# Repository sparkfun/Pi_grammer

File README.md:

SparkFun Pi AVR Programmer HAT
========================================

[*SparkFun Pi AVR Programmer HAT (DEV-14747)*](https://www.sparkfun.com/products/14747)

A shield for Raspberry Pi 2, used for programming AVR ICs. Includes capsense pad to engage, 2x3 ISP header for connectivity and status LEDs.

Documentation
--------------
* **[Hookup Guide](https://learn.sparkfun.com/tutorials/pi-avr-programmer-hat-hookup-guide)** - Basic hookup guide for the Pi AVR Programmer Hat.
* **[Raspberry Pi Stand-Alone Programmer](https://learn.sparkfun.com/tutorials/raspberry-pi-stand-alone-programmer)** - more information about the prototype can be found in the article.

Additional Notes
--------------
This project originated from Adafruits tutorial here:

https://learn.adafruit.com/program-an-avr-or-arduino-using-raspberry-pi-gpio-pins/overview

This shield makes it a bit easier to program AVRs with a headless Raspberry Pi.

This repo also contains some other useful files:

* **RCLOCAL** - calls /home/pi/test.py and ensure that this python module will run automatically at boot up (useful when running headless)

* **AVRDUDE config file** - sets the GPIO used for programming (in avrdude) to work with the shield design. It's located at the very end of this file.

* **test.py** - the python module that is auto called during bootup. This also listens to the capsense IC and engages programming when p ressed.

**Note:** test.py called pi_program.sh to actually begin programming.

**Note:** test.py also checks for MEDIA drives plugged into the USB ports of the Raspi. If there is a HEX file on the MEDIA drive (any name, it just has to have the ".hex" extension) it will copy it in and use that for programming.

KEYWORDS: RASPI PROGRAMMER

Troubleshooting Tips
--------------

1) USB port issues. If you are having trouble with com port enumeration. That is, you are plugging in something like an FTDI serial basic, and the Raspi will not recognize it. This may be fixed by using one of SparkFun Cerberus USB hub cables. We found that after plugging in 20+ FTDI basics into a pi, then it stops recognizing the devices. But if you use a hub (like the cerberus) inbetween the pi USB and the serial bridge IC, then it always pops up as "/dev/ttyUSB0" for 1000s of boards in a row. Wahoo!

[SparkFun Cerberus USB Cable](https://www.sparkfun.com/products/12016)

License Information
-------------------

This product is _**open source**_! 

Please review the LICENSE.md file for license information. 

If you have any questions or concerns on licensing, please contact techsupport@sparkfun.com.

Distributed as-is; no warranty is given.

- Your friends at SparkFun.

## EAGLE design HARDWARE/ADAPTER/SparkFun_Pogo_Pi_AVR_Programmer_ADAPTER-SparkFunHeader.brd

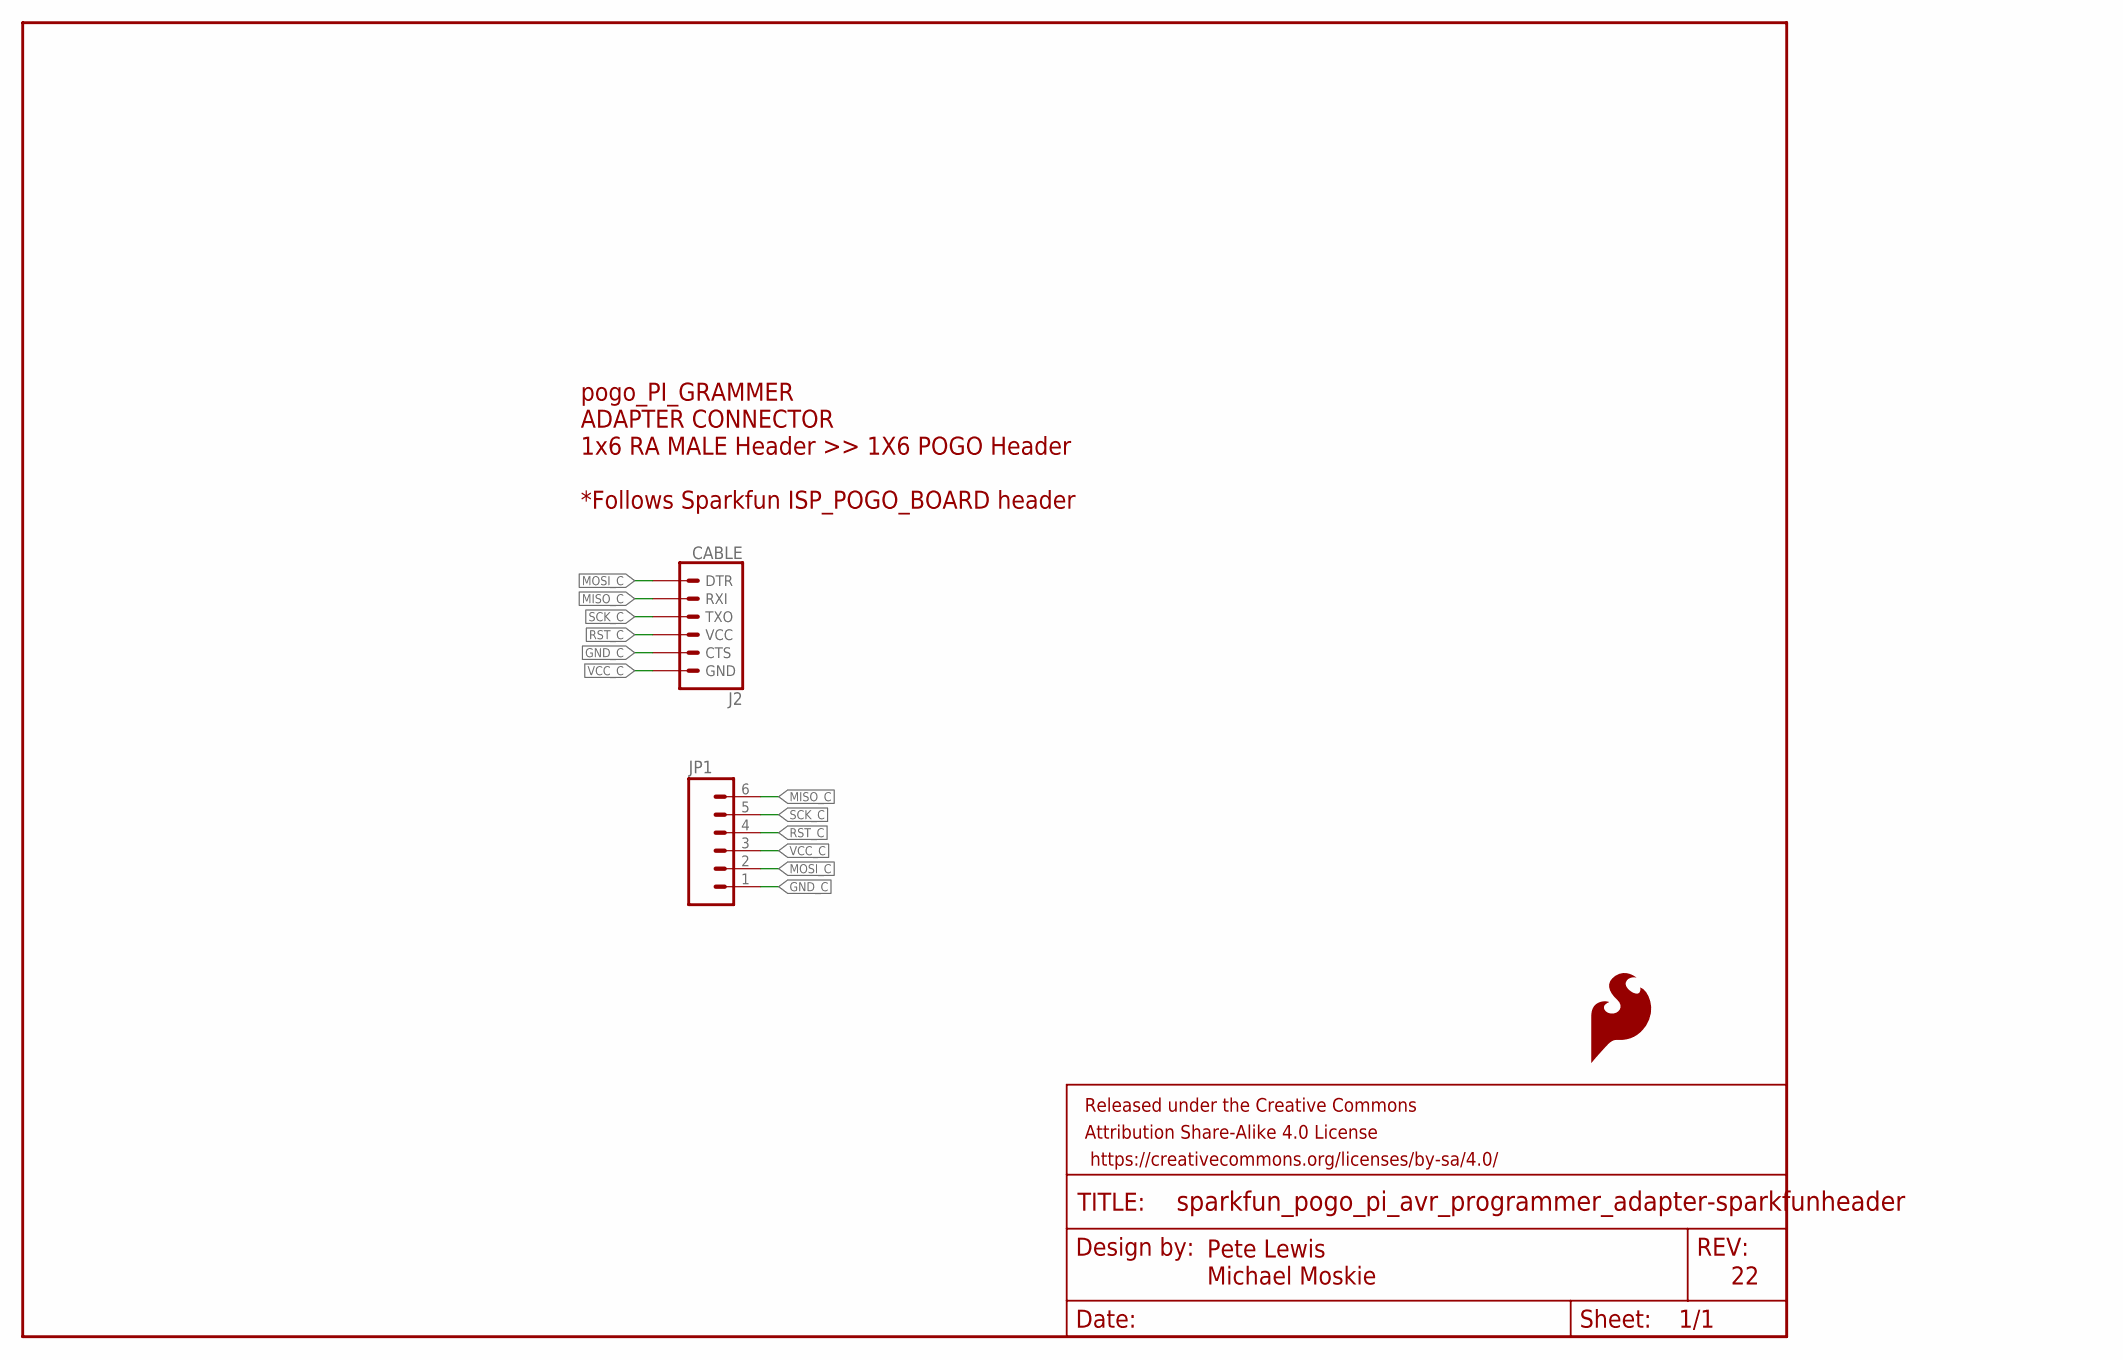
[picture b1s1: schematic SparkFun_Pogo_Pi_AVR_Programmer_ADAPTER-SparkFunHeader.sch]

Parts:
FRAME1: FRAME-LETTER; CREATIVE_COMMONS
J2: CABLE; 1X06-SMD_RA_MALE
JP1: M06POLAR; MOLEX-1X6
LOGO1: SFE_LOGO_FLAME.1_INCH; SFE_LOGO_FLAME_.1

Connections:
GND_C: J2.5 (CTS), JP1.1
MISO_C: J2.2 (RXI), JP1.6
MOSI_C: J2.1 (DTR), JP1.2
RST_C: J2.4 (VCC), JP1.4
SCK_C: J2.3 (TXO), JP1.5
VCC_C: J2.6 (GND), JP1.3

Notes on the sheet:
pogo_PI_GRAMMER ADAPTER CONNECTOR 1x6 RA MALE Header >> 1X6 POGO Header *Follows Sparkfun ISP_POGO_BOARD header
Pete Lewis Michael Moskie

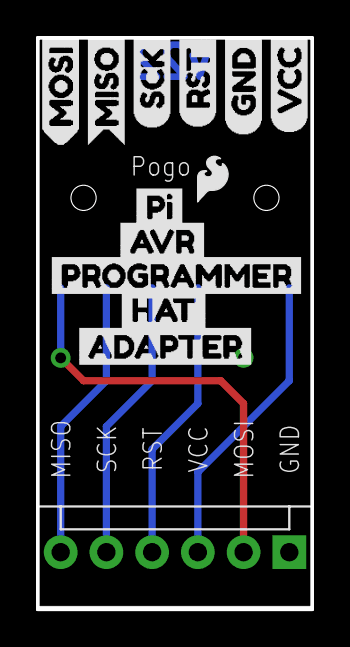
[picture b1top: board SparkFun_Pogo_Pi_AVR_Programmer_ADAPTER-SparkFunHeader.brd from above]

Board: 2 copper layers, 15.2 x 31.8 mm, 15 parts (1 on the bottom side), 6 nets.

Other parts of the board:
U$1: GND1
U$2: MISO5
U$3: MOSI4
U$4: RST2
U$5: SCK3
U$6: VCC0
U$7: PI0
U$8: AVR1
U$9: PROGRAMMER2
U$10: HAT3
U$11: ADAPTER4

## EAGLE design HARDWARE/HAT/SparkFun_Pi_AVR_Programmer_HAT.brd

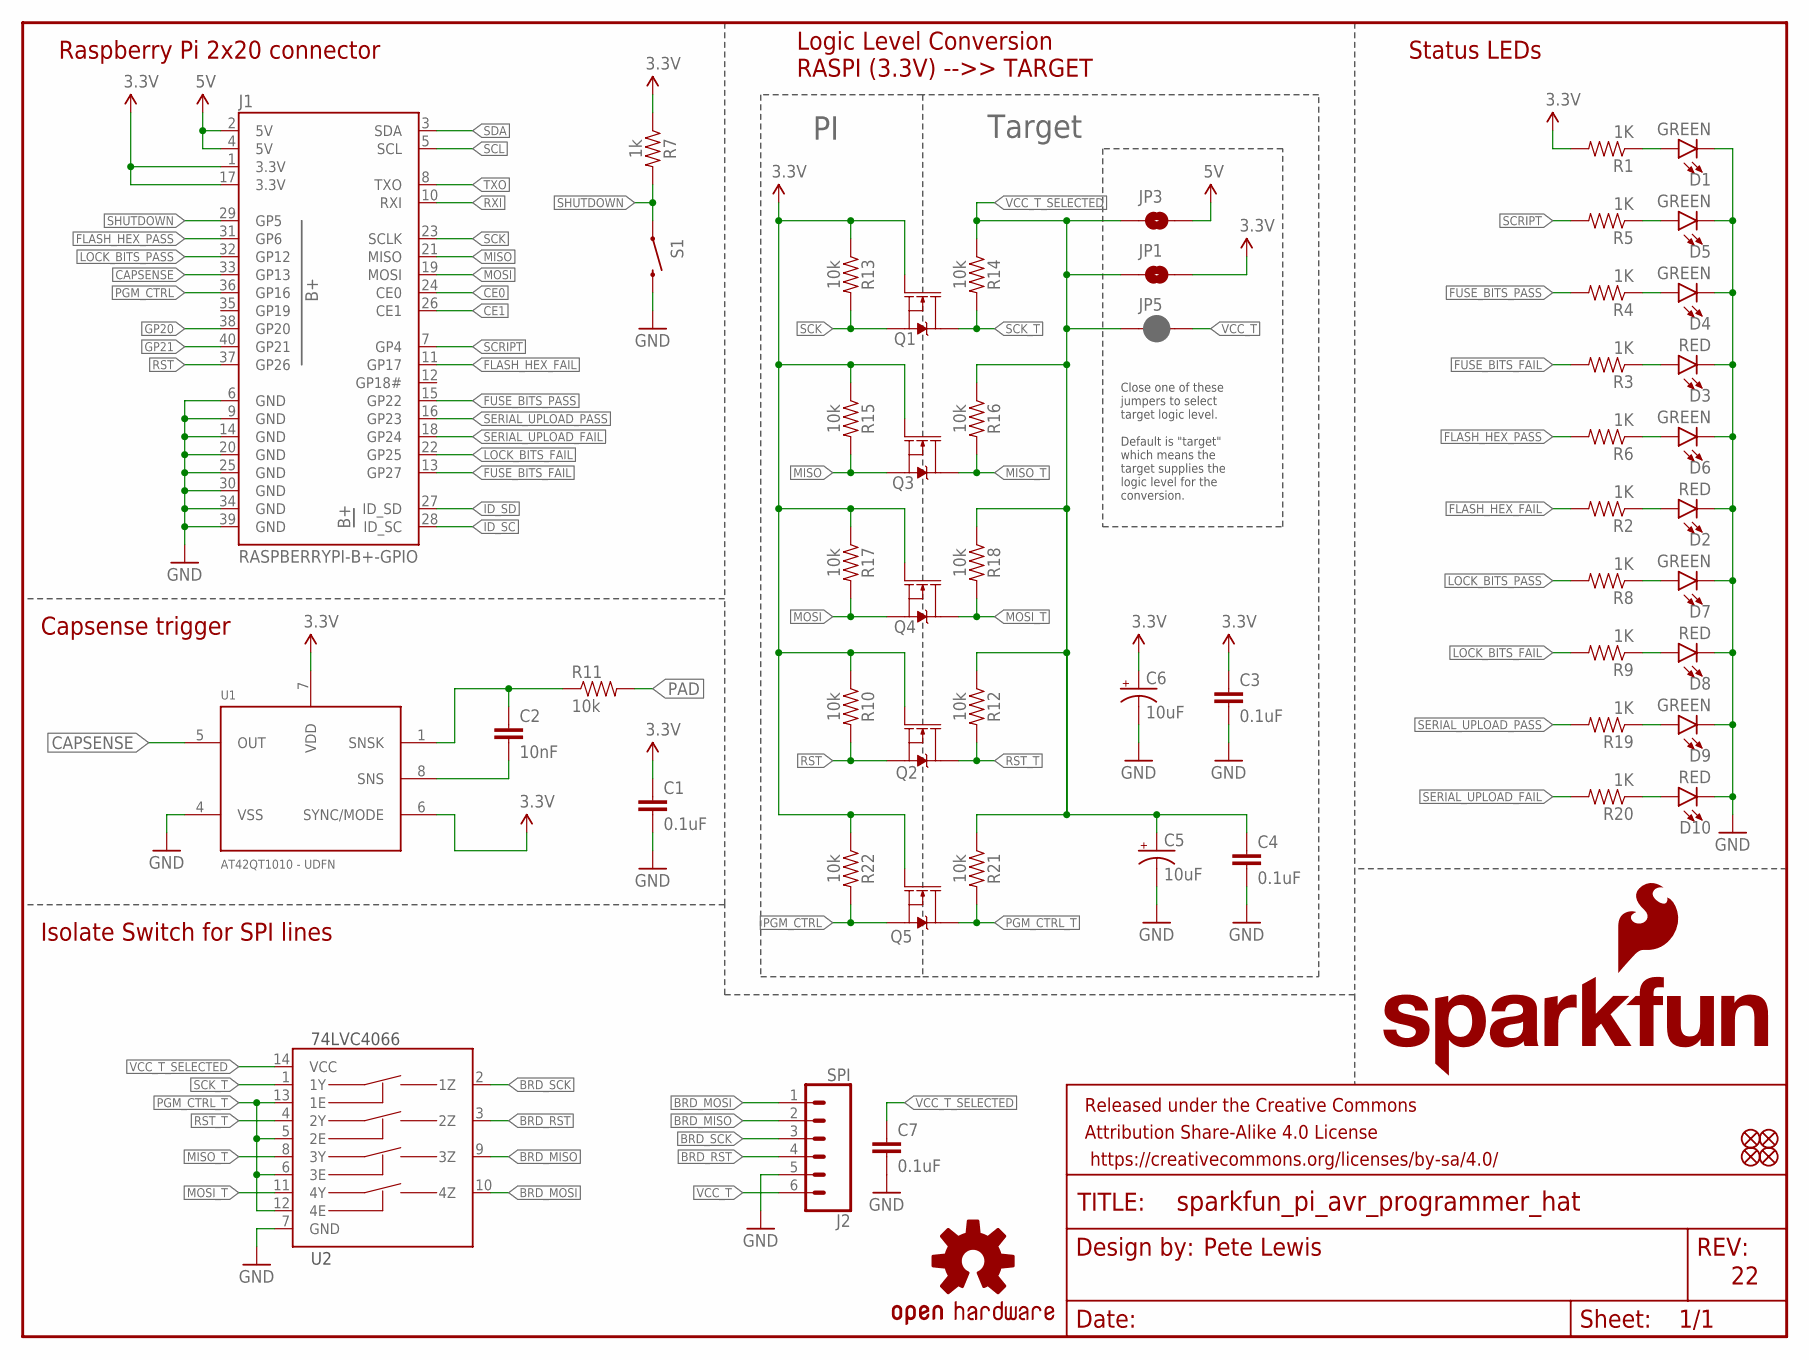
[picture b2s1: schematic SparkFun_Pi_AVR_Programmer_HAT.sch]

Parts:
C1: 0.1uF; 0603-CAP
C2: 10nF; 0603-CAP
C3, C4, C7: 0.1uF; 0603
C5, C6: 10uF; EIA3216
D1, D4, D5, D6, D7, D9: GREEN; LED-1206
D2, D3, D8, D10: RED; LED-1206
FD1, FD2, FD3, FD4: FIDUCIALUFIDUCIAL; FIDUCIAL-MICRO
FRAME1: FRAME-LETTER; CREATIVE_COMMONS
J1: RASPBERRYPI-B+-GPIO; 2X20-SHROUDED
J2: SPI; 1X06-SMD_RA_MALE
JP1, JP3: JUMPER-SMT_2_NO_SILK; SMT-JUMPER_2_NO_SILK
JP5: JUMPER-SMT_2_NC_PASTE_SILK; SMT-JUMPER_2_NC_PASTE_SILK
LOGO1: SFE_LOGO_FLAME.2_INCH; SFE_LOGO_FLAME_.2
LOGO2: OSHW-LOGOL; OSHW-LOGO-L
LOGO3: SFE_LOGO_NAME.6_INCH; SFE_LOGO_NAME_.6
Q1, Q2, Q3, Q4, Q5: 220mA/50V/3.5Ω; SOT23-3
R1, R2, R3, R4, R5, R6, R8, R9, R19, R20: 1K; 0603-RES
R7: 1k; 0603
R10, R12, R13, R14, R15, R16, R17, R18, R21, R22: 10k; 0603
R11: 10k; 0603-RES
S1: SWITCH-MOMENTARY-2SMD; TACTILE-SWITCH-SMD
U1: AT42QT1010 - UDFN; UDFN/USON_8_PAD
U2: 74LVC4066; SO14

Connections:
3.3V: C1.1, C3.1, C6.+, J1.1 (3.3V), J1.17 (3.3V), JP1.2, Q1.1 (G), Q2.1 (G), Q3.1 (G), Q4.1 (G), Q5.1 (G), R1.2, R7.1, R10.1, R13.1, R15.1, R17.1, R22.1, U1.6 (SYNC/MODE), U1.7 (VDD)
5V: J1.2 (5V), J1.4 (5V), JP3.2
BRD_MISO: J2.2, U2.9 (3Z)
BRD_MOSI: J2.1, U2.10 (4Z)
BRD_RST: J2.4, U2.3 (2Z)
BRD_SCK: J2.3, U2.2 (1Z)
CAPSENSE: J1.33 (GP13), U1.5 (OUT)
CE0: J1.24 (CE0)
CE1: J1.26 (CE1)
FLASH_HEX_FAIL: J1.11 (GP17), R2.2
FLASH_HEX_PASS: J1.31 (GP6), R6.2
FUSE_BITS_FAIL: J1.13 (GP27), R3.2
FUSE_BITS_PASS: J1.15 (GP22), R4.2
GND: C1.2, C3.2, C4.2, C5.-, C6.-, C7.2, D1.C, D2.C, D3.C, D4.C, D5.C, D6.C, D7.C, D8.C, D9.C, D10.C, J1.6 (GND), J1.9 (GND), J1.14 (GND), J1.20 (GND), J1.25 (GND), J1.30 (GND), J1.34 (GND), J1.39 (GND), J2.5, S1.3 (2), U1.4 (VSS), U2.7 (GND)
GP20: J1.38 (GP20)
GP21: J1.40 (GP21)
ID_SC: J1.28 (ID_SC)
ID_SD: J1.27 (ID_SD)
LOCK_BITS_FAIL: J1.22 (GP25), R9.2
LOCK_BITS_PASS: J1.32 (GP12), R8.2
MISO: J1.21 (MISO), Q3.2 (S), R15.2
MISO_T: Q3.3 (D), R16.2, U2.8 (3Y)
MOSI: J1.19 (MOSI), Q4.2 (S), R17.2
MOSI_T: Q4.3 (D), R18.2, U2.11 (4Y)
unnamed: D6.A, R6.1
unnamed: D1.A, R1.1
unnamed: D2.A, R2.1
unnamed: D3.A, R3.1
unnamed: D7.A, R8.1
unnamed: D4.A, R4.1
unnamed: D5.A, R5.1
unnamed: D8.A, R9.1
unnamed: C2.2, U1.8 (SNS)
unnamed: C2.1, R11.1, U1.1 (SNSK)
unnamed: D9.A, R19.1
unnamed: D10.A, R20.1
PAD: R11.2
PGM_CTRL: J1.36 (GP16), Q5.2 (S), R22.2
PGM_CTRL_T: Q5.3 (D), R21.2, U2.5 (2E), U2.6 (3E), U2.12 (4E), U2.13 (1E)
RST: J1.37 (GP26), Q2.2 (S), R10.2
RST_T: Q2.3 (D), R12.2, U2.4 (2Y)
RXI: J1.10 (RXI)
SCK: J1.23 (SCLK), Q1.2 (S), R13.2
SCK_T: Q1.3 (D), R14.2, U2.1 (1Y)
SCL: J1.5 (SCL)
SCRIPT: J1.7 (GP4), R5.2
SDA: J1.3 (SDA)
SERIAL_UPLOAD_FAIL: J1.18 (GP24), R20.2
SERIAL_UPLOAD_PASS: J1.16 (GP23), R19.2
SHUTDOWN: J1.29 (GP5), R7.2, S1.1
TXO: J1.8 (TXO)
VCC_T: J2.6, JP5.2
VCC_T_SELECTED: C4.1, C5.+, C7.1, JP1.1, JP3.1, JP5.1, R12.1, R14.1, R16.1, R18.1, R21.1, U2.14 (VCC)

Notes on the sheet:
Raspberry Pi 2x20 connector
Pete Lewis
Status LEDs
Capsense trigger
Target
Logic Level Conversion RASPI (3.3V) -->> TARGET
Isolate Switch for SPI lines
Close one of these jumpers to select target logic level. Default is "target" which means the target supplies the logic level for the conversion.

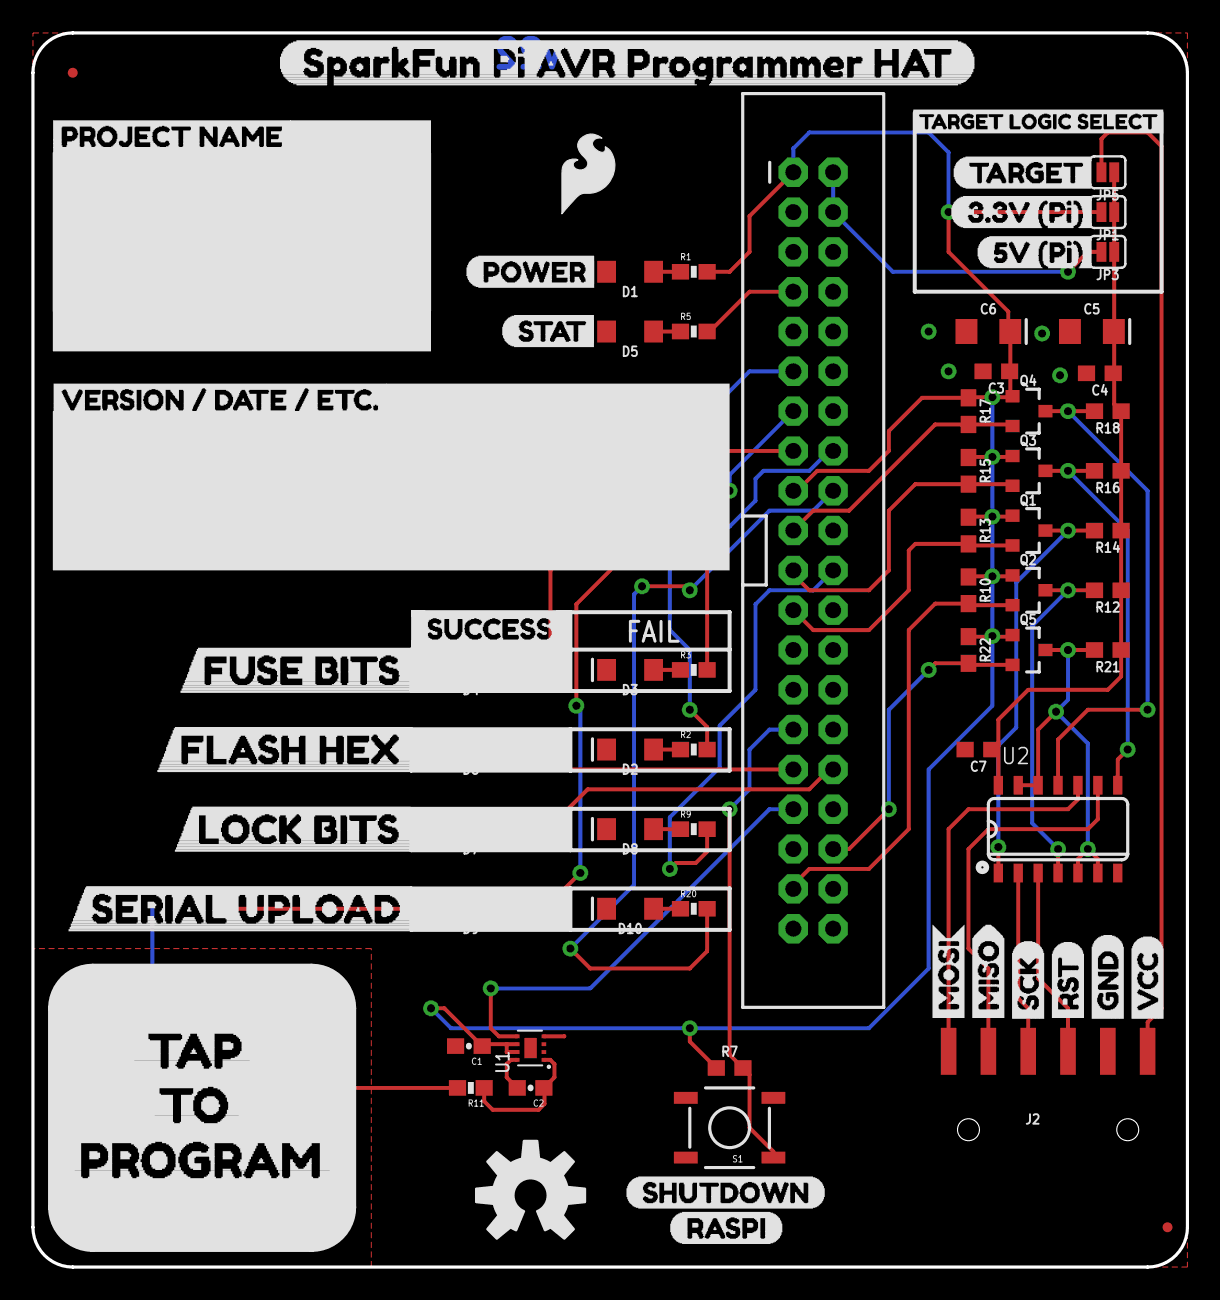
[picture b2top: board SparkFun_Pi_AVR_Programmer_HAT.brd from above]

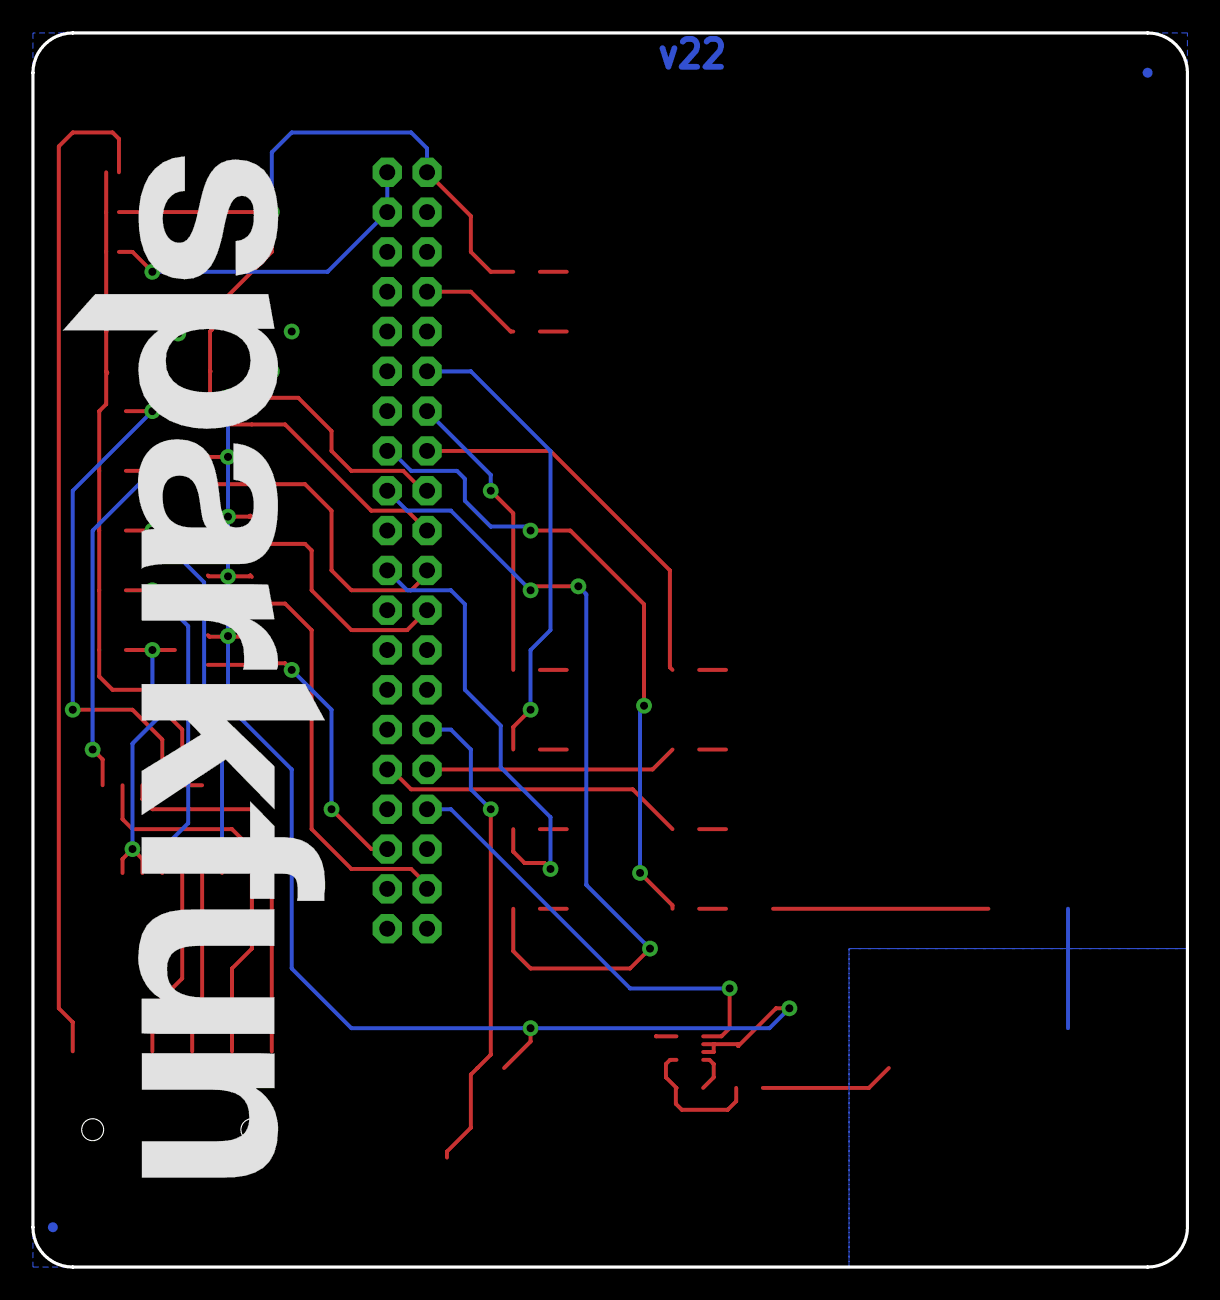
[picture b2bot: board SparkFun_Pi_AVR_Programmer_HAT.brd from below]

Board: 2 copper layers, 73.7 x 78.7 mm, 85 parts (3 on the bottom side), 42 nets.

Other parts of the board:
U$1: SPARKFUN_PI_AVR_PROGRAMMER_HAT0
U$2: PROJECT_NAME0
U$3: VERSION_#_DATE_#_ETC#0
U$4: TARGET_LOGIC_SELECT4
U$5: POWER0
U$6: STAT1
U$7: SHUTDOWN2
U$8: RASPI3
U$9: 3#3V_#PI#7
U$10: 5V_#PI#8
U$11: TARGET0
U$12: MISO1
U$13: MOSI0
U$14: SCK2
U$15: RST3
U$16: GND4
U$18: TAP0
U$19: TO1
U$20: PROGRAM2
U$21: VCC0
U$22: SUCCESS0
U$23: FUSE_BITS2
U$24: FLASH_HEX3
U$25: LOCK_BITS4
U$26: SERIAL_UPLOAD5

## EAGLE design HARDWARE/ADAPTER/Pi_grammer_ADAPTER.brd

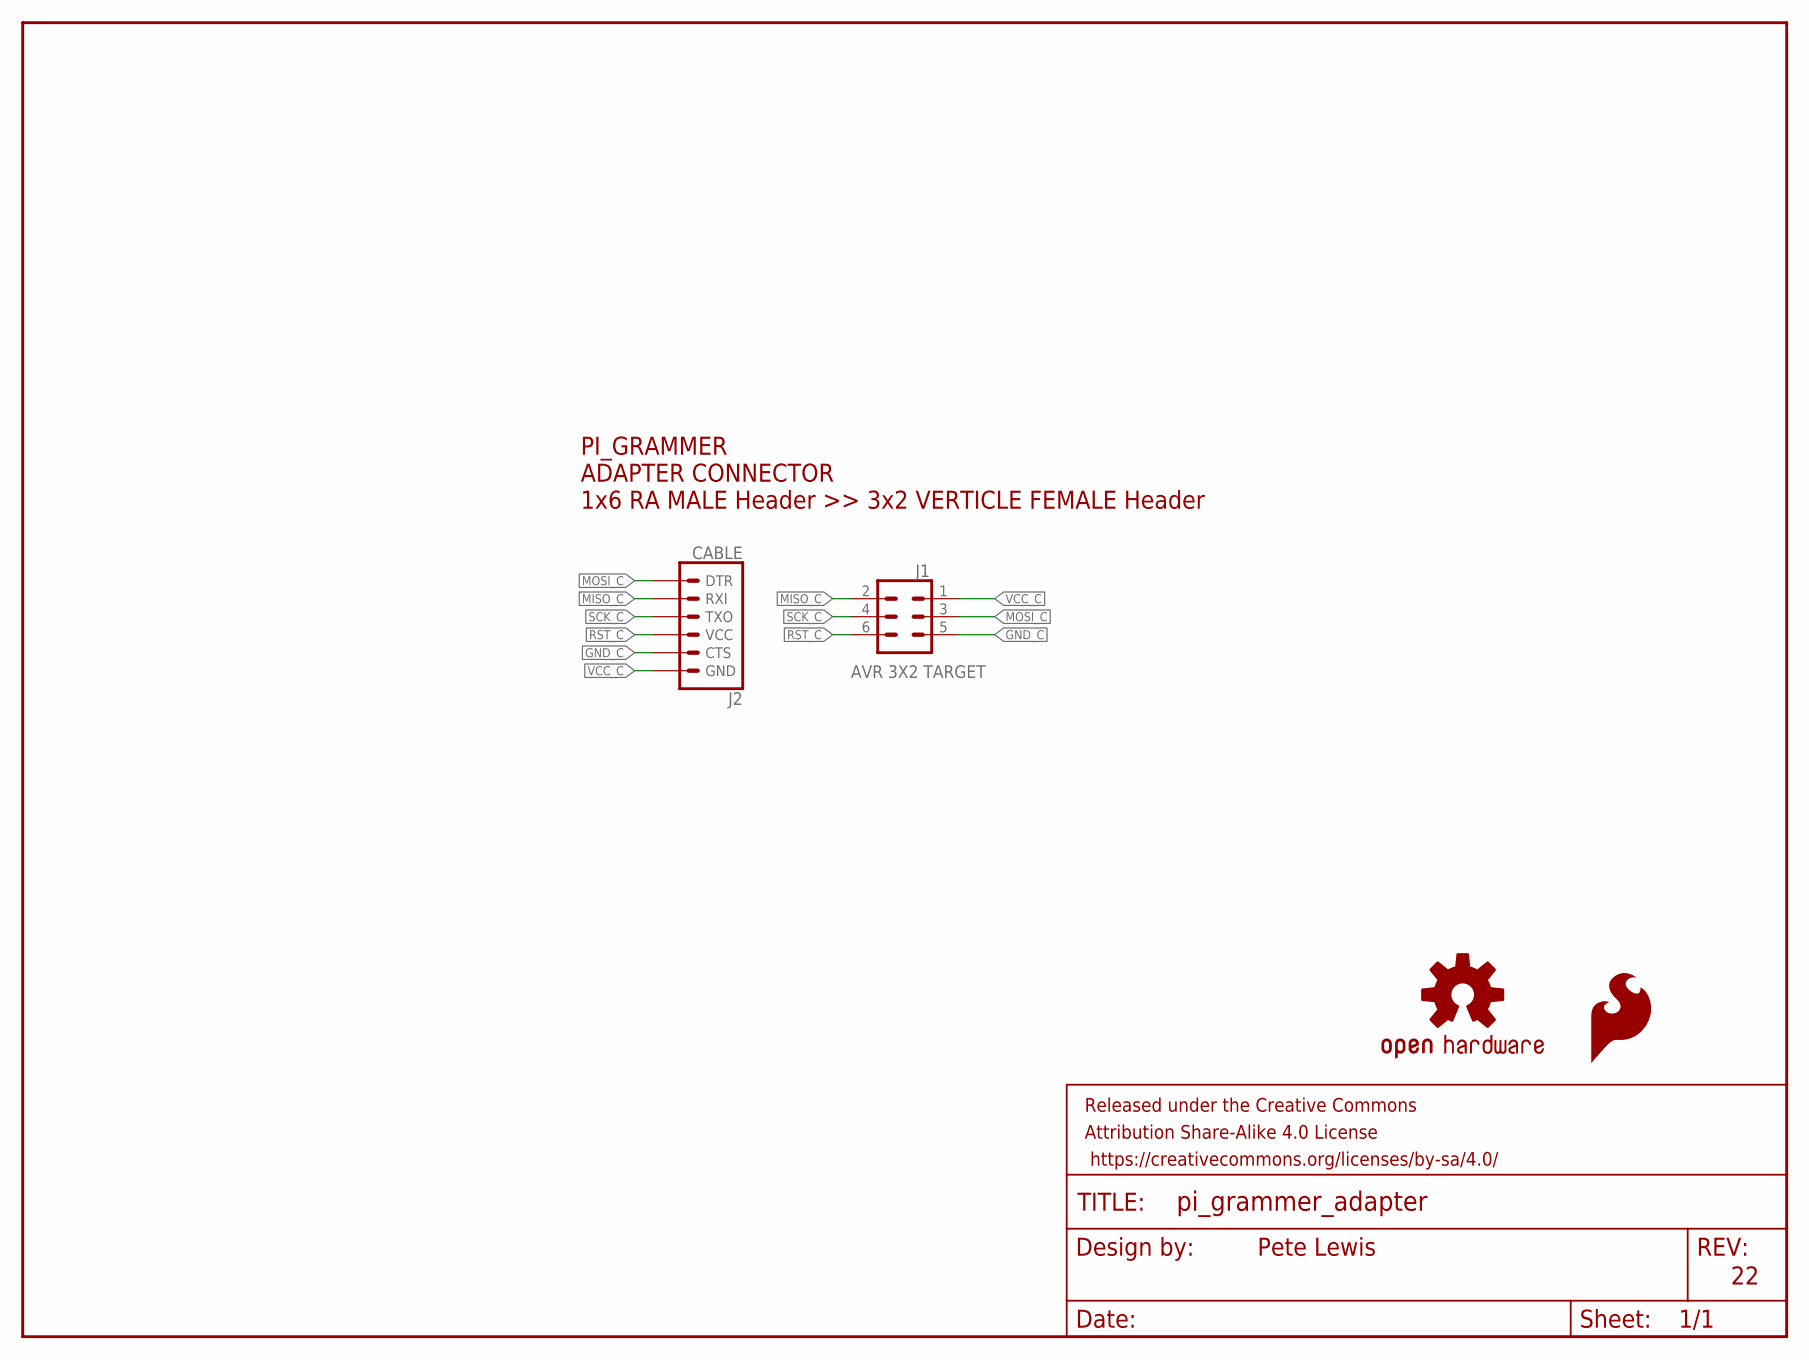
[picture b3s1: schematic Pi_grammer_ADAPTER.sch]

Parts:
FRAME1: FRAME-LETTER; CREATIVE_COMMONS
J1: AVR 3X2 TARGET; 2X3_SMT_POSTS
J2: CABLE; 1X06-SMD_RA_MALE
LOGO1: SFE_LOGO_FLAME.1_INCH; SFE_LOGO_FLAME_.1
LOGO2: OSHW-LOGOMINI; OSHW-LOGO-MINI

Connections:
GND_C: J1.5, J2.5 (CTS)
MISO_C: J1.2, J2.2 (RXI)
MOSI_C: J1.3, J2.1 (DTR)
RST_C: J1.6, J2.4 (VCC)
SCK_C: J1.4, J2.3 (TXO)
VCC_C: J1.1, J2.6 (GND)

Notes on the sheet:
PI_GRAMMER ADAPTER CONNECTOR 1x6 RA MALE Header >> 3x2 VERTICLE FEMALE Header
Pete Lewis

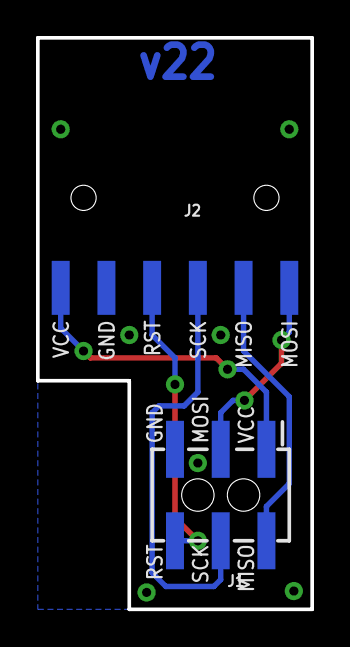
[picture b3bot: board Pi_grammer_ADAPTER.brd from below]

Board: 2 copper layers, 15.2 x 31.8 mm, 5 parts (2 on the bottom side), 6 nets.

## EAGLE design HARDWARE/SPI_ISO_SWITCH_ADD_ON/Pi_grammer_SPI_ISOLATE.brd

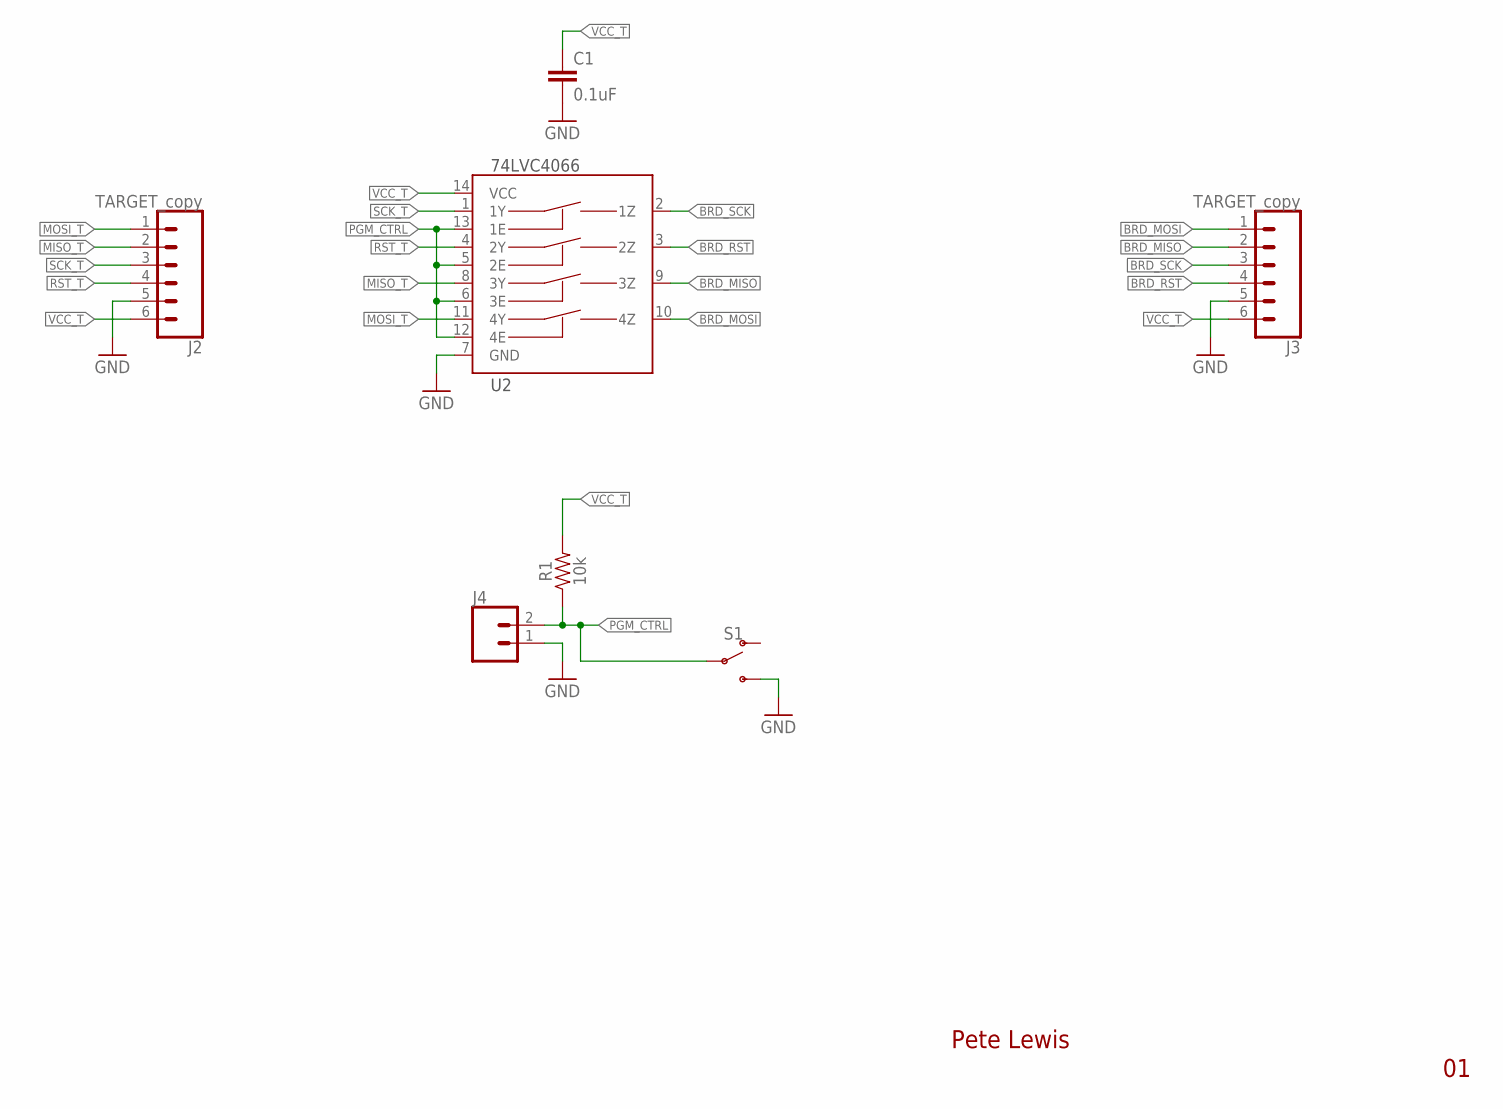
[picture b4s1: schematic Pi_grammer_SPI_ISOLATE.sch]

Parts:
C1: 0.1uF; 0603
J2, J3: TARGET_copy; 1X06_LOCK
J4: CONN_02; 1X02
R1: 10k; 0603
S1: SWITCH-SPDT-PTH-11.6X4.0MM-LOCK; SWITCH_SPDT_PTH_11.6X4.0MM_LOCK
U2: 74LVC4066; SO14

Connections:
BRD_MISO: J3.2, U2.9 (3Z)
BRD_MOSI: J3.1, U2.10 (4Z)
BRD_RST: J3.4, U2.3 (2Z)
BRD_SCK: J3.3, U2.2 (1Z)
GND: C1.2, J2.5, J3.5, J4.1, S1.3 (S), U2.7 (GND)
MISO_T: J2.2, U2.8 (3Y)
MOSI_T: J2.1, U2.11 (4Y)
PGM_CTRL: J4.2, R1.1, S1.2, U2.5 (2E), U2.6 (3E), U2.12 (4E), U2.13 (1E)
RST_T: J2.4, U2.4 (2Y)
SCK_T: J2.3, U2.1 (1Y)
VCC_T: C1.1, J2.6, J3.6, R1.2, U2.14 (VCC)

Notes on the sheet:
Pete Lewis

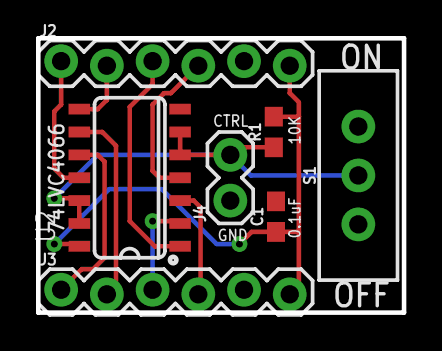
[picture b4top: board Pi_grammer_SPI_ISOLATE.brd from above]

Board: 2 copper layers, 20.3 x 15.2 mm, 7 parts (0 on the bottom side), 11 nets.

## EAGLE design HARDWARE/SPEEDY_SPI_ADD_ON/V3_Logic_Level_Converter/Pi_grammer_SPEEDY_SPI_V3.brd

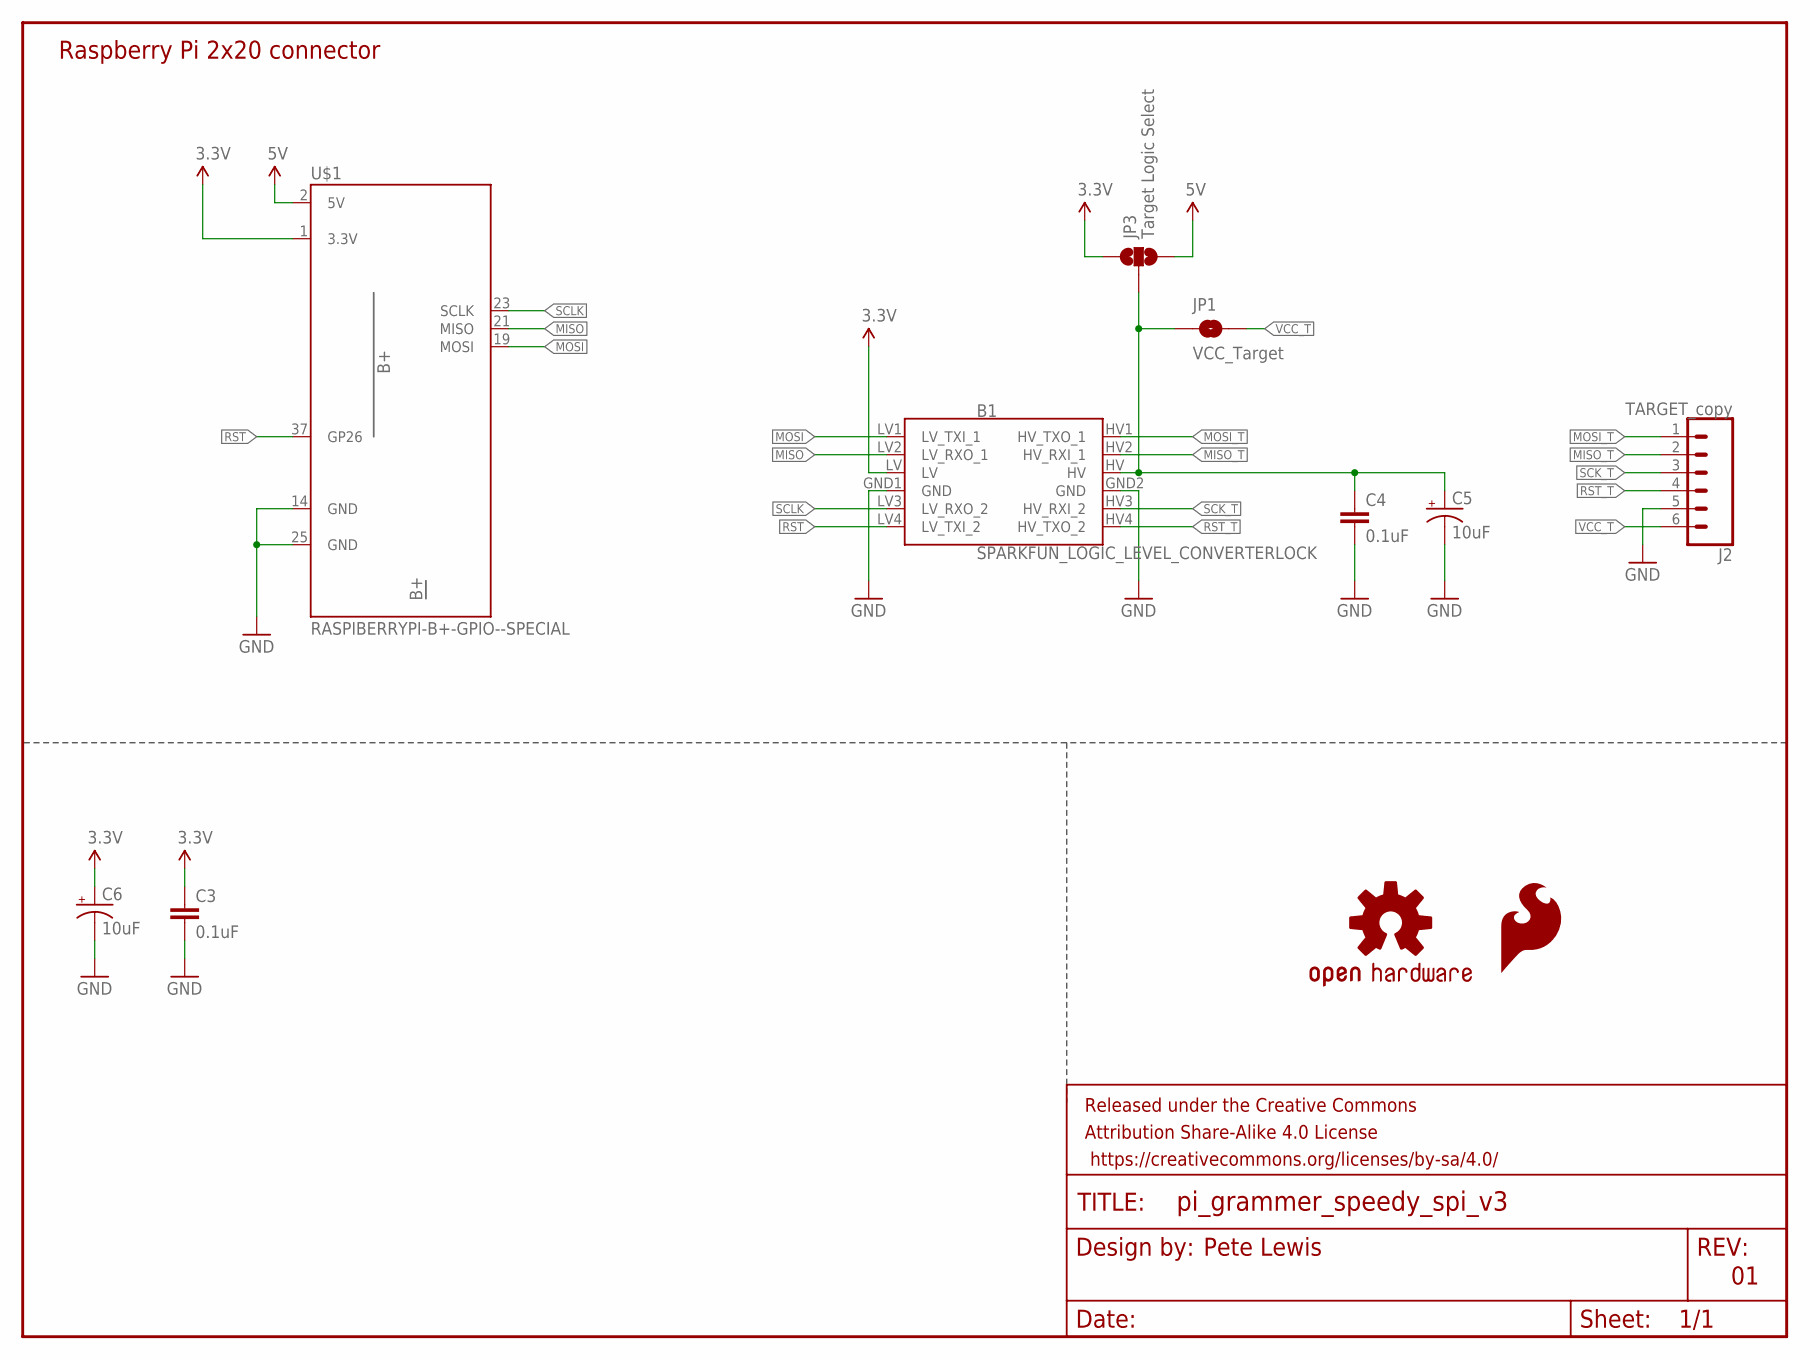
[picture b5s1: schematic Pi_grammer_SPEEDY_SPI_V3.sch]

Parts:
B1: SPARKFUN_LOGIC_LEVEL_CONVERTERLOCK; SPARKFUN_LOGIC_LEVEL_CONVERTER_LOCK
C3, C4: 0.1uF; 0603
C5, C6: 10uF; EIA3216
FRAME1: FRAME-LETTER; CREATIVE_COMMONS
J2: TARGET_copy; 1X06-SIP_LOCK
JP1: VCC_Target; SMT-JUMPER_2_NO_SILK
JP3: Target Logic Select; SMT-JUMPER_3_NO_SILK
LOGO1: SFE_LOGO_FLAME.1_INCH; SFE_LOGO_FLAME_.1
LOGO2: OSHW-LOGOS; OSHW-LOGO-S
U$1: RASPIBERRYPI-B+-GPIO--SPECIAL; 2X20-SHROUDED--SPECIAL

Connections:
3.3V: B1.LV, C3.1, C6.+, JP3.1, U$1.1 (3.3V)
5V: JP3.3, U$1.2 (5V)
GND: B1.GND1 (GND), B1.GND2 (GND), C3.2, C4.2, C5.-, C6.-, J2.5, U$1.14 (GND), U$1.25 (GND)
MISO: B1.LV2 (LV_RXO_1), U$1.21 (MISO)
MISO_T: B1.HV2 (HV_RXI_1), J2.2
MOSI: B1.LV1 (LV_TXI_1), U$1.19 (MOSI)
MOSI_T: B1.HV1 (HV_TXO_1), J2.1
unnamed: B1.HV, C4.1, C5.+, JP1.1, JP3.2
RST: B1.LV4 (LV_TXI_2), U$1.37 (GP26)
RST_T: B1.HV4 (HV_TXO_2), J2.4
SCK_T: B1.HV3 (HV_RXI_2), J2.3
SCLK: B1.LV3 (LV_RXO_2), U$1.23 (SCLK)
VCC_T: J2.6, JP1.2

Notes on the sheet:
Raspberry Pi 2x20 connector
Pete Lewis

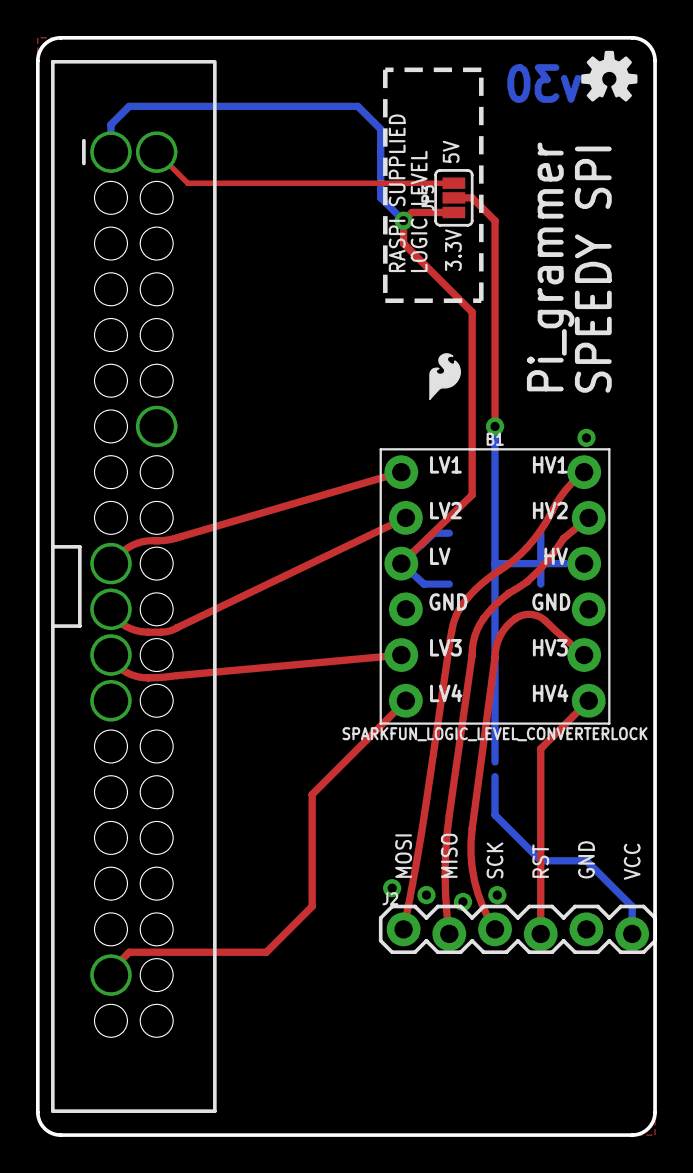
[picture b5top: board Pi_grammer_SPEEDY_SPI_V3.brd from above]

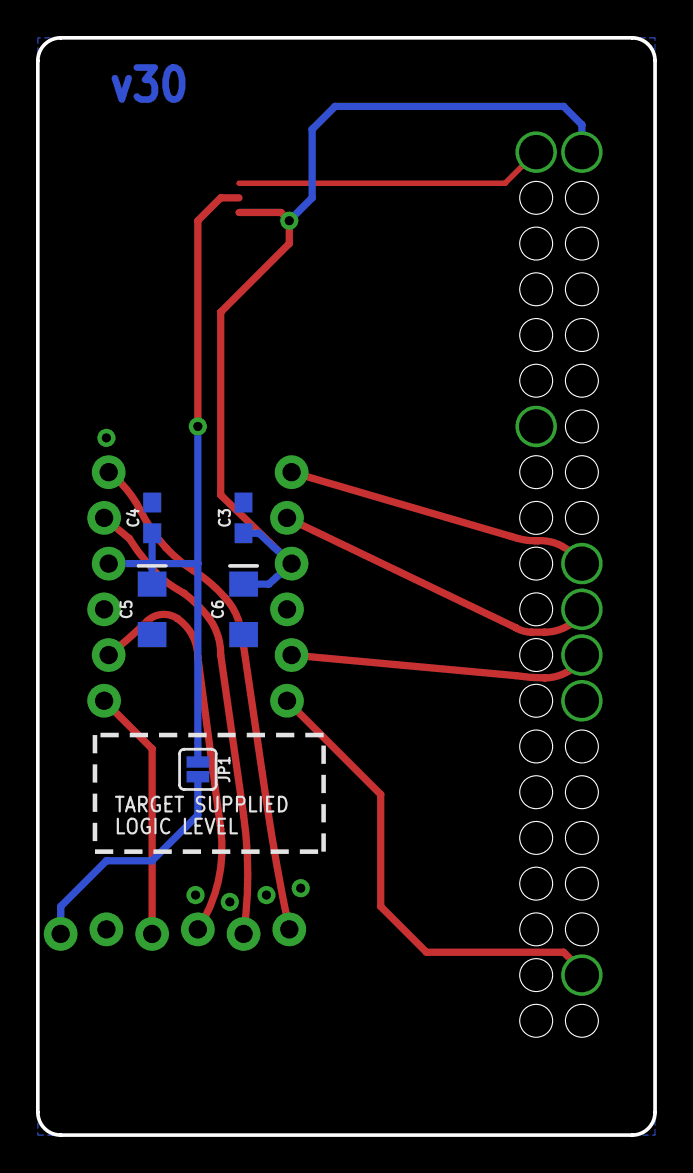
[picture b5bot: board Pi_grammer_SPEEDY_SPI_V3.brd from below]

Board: 2 copper layers, 34.3 x 61.0 mm, 12 parts (5 on the bottom side), 13 nets.

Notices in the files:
parts and their libraries:
SparkFun-Aesthetics: Licensing: CC v3.0 Share-Alike You are welcome to use this library for commercial purposes.
SparkFun-Aesthetics: Released under the Creative Commons Attribution Share-Alike 4.0 License
SparkFun-Aesthetics: https://creativecommons.org/licenses/by-sa/4.0
